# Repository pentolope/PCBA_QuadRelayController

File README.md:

# Four-Channel Relay Controller

Four-channel relay controller run by a small MCU on 5 V logic, switching external loads through screw terminals with the switched side kept apart from logic.

This repository seeds the design of a four-channel relay controller operated by a small MCU, with 5 V logic power and each relay switching an external load through screw terminals. The brief fixes the functional block list — input protection, transistor/MOSFET relay drivers, flyback suppression, status indication, and a programming interface — and imposes one layout-level constraint: the switched side must be physically separated from the logic side, with conservative clearances appropriate to a voltage rating the design agent selects and documents. Beyond those items nothing is pinned down. No relay, MCU, driver device, terminal block, protection part, programming standard, board outline, or stackup is named. The switched-side voltage rating is explicitly delegated — it is one "you select and document" — while the switched-side current rating and whether the load is AC or DC are never mentioned at all, and so are open by silence. Most of the architecture therefore belongs to the design agent; the brief supplies the block list and the separation constraint, not the implementation.

> **This board has not been designed.** There is no schematic, no layout and no
> part selection here — only the brief, a reading of the brief, and the
> scaffolding a design run needs. That is the intended state of this repository,
> not a gap in it.

## What the brief fixes, and what it leaves open

The brief pins down 13 requirements and deliberately leaves
20 decisions to whoever designs the board. The `Source` column says
which is which: `brief` is quoted from [BRIEF.md](BRIEF.md), `metadata` comes
from the benchmark catalogue, and `open` means the brief does not fix it.

| Aspect | Value | Source |
|---|---|---|
| Channel count | Four relay channels | brief |
| Controller | A small MCU; no family, part, package or core named | brief |
| Logic supply | 5 V | brief |
| Load connection | Each relay switches an external load through screw terminals | brief |
| Relay driver stage | Transistor/MOSFET relay drivers required; device and topology unspecified | brief |
| Flyback suppression | Required; suppression method not specified | brief |
| Input protection | Required; protected nodes and scheme not specified | brief |
| Status indication and programming interface | Both required; indication form, programming standard and the physical form of the interface all unspecified | brief |
| High/low voltage partition | Switched side physically separated from logic side | brief |
| Switched-side voltage rating, current rating and clearance values | Not fixed by the brief; the design agent selects and documents the voltage rating and chooses conservative clearances appropriate to it. The current rating and whether the load is AC or DC are not mentioned at all and are equally the agent's to decide. | open |
| Relay selection (coil voltage, contact form and rating, mounting style) | Design agent's choice; the brief names no relay | open |
| Board outline, size, mounting and terminal pitch | Design agent's choice; the brief states no mechanical envelope | open |
| Likely layer count | 2 | metadata |
| Category / difficulty / brief detail | industrial-control; difficulty 2; detail 2 | metadata |

The full split, with the verbatim brief text substantiating every fixed
requirement, is in [board/requirements.md](board/requirements.md) and
machine-readably in [board/requirements.json](board/requirements.json).

**Missing details are design freedom, not permission to fabricate unstated user
requirements.** A choice the brief left open is recorded as a decision, with its
reasoning — never promoted into a requirement.

## Benchmark position

| | |
|---|---|
| Benchmark id | 3 of 32 |
| Category | industrial-control |
| Difficulty | 2 / 5 |
| Brief detail | 2 / 5 |
| Likely layer count | 2 |
| Primary stressors | high/low voltage partition, relay flyback, creepage/clearance, terminal placement |

At difficulty 2 and detail 2 in the industrial-control category, this board tests whether an agent can execute a conventionally-shaped circuit while getting the physical discipline right rather than the component novelty. The listed stressors — high/low voltage partition, relay flyback, creepage/clearance, terminal placement — are all layout and rating problems, and the brief deliberately withholds the switched-side voltage rating so the agent must select one, choose clearances that are conservative and appropriate to it, and live with the consequences in the floorplan. The real test is whether the separation barrier and the clearance numbers rest on a stated basis or are merely asserted.

This repository is one of thirty-two. The suite, the protocol and the results
live in [PCBA_AutoDesignAndTest_Bench](https://github.com/pentolope/PCBA_AutoDesignAndTest_Bench).

## Repository layout

| Path | Contents |
|---|---|
| `BRIEF.md` | the supplied brief — authoritative, preserved byte for byte, never edited |
| `board/requirements.md` | what the brief fixes, what it leaves open, and where decisions get recorded |
| `board/requirements.json` | the same split, machine-readable, each fixed requirement bound to brief text |
| `board/manifest.template.json` | the toolkit's minimum manifest, pre-filled for this board |
| `board/toolchain.json` | where this board's build finds KiCad and the router |
| `benchmark/metadata.json` | the supplied catalogue entry — category, difficulty, detail, stressors |
| `docs/architecture.md` | the decisions this board must make, as questions, unanswered |
| `docs/sources.md` | the classes of evidence the design will have to cite |
| `docs/status.md` | what exists, what does not, and what is deliberately absent |
| `candidates/` | disposable search output, ignored by Git |
| `.claude/skills/` | the accountability-review skill [CLAUDE.md](CLAUDE.md) requires before a push |
| `tooling/PCBA_AutoDesignAndTest` | the shared verification/routing/release toolkit, as a pinned submodule |

## Getting the repository

The toolkit is a submodule and carries KiCad Routing Tools as a submodule of its
own, so clone recursively:

```bash
git clone --recursive https://github.com/pentolope/PCBA_QuadRelayController.git
```

```bash
git submodule update --init --recursive
```

## Designing the board

Generic verification, routing and release logic is **not** written here. It is
consumed from `tooling/PCBA_AutoDesignAndTest`, which is board-agnostic by
construction and must stay that way; this repository owns the board and nothing
else. Start from
[the toolkit's onboarding guide](tooling/PCBA_AutoDesignAndTest/examples/onboarding.md),
and see [CLAUDE.md](CLAUDE.md) for the rules a design run works under.

```bash
python3 tooling/PCBA_AutoDesignAndTest/run.py preflight
```

## Brief integrity

`BRIEF.md` SHA-256 `7ed0a0647777bf47b7bdb843b795a63dda5a91aa048535087b107b13f95b585d`

Every quotation in `board/requirements.json` is bound to those exact bytes. If
the brief ever changes, the bindings are stale by construction — which is the
point of recording the digest.

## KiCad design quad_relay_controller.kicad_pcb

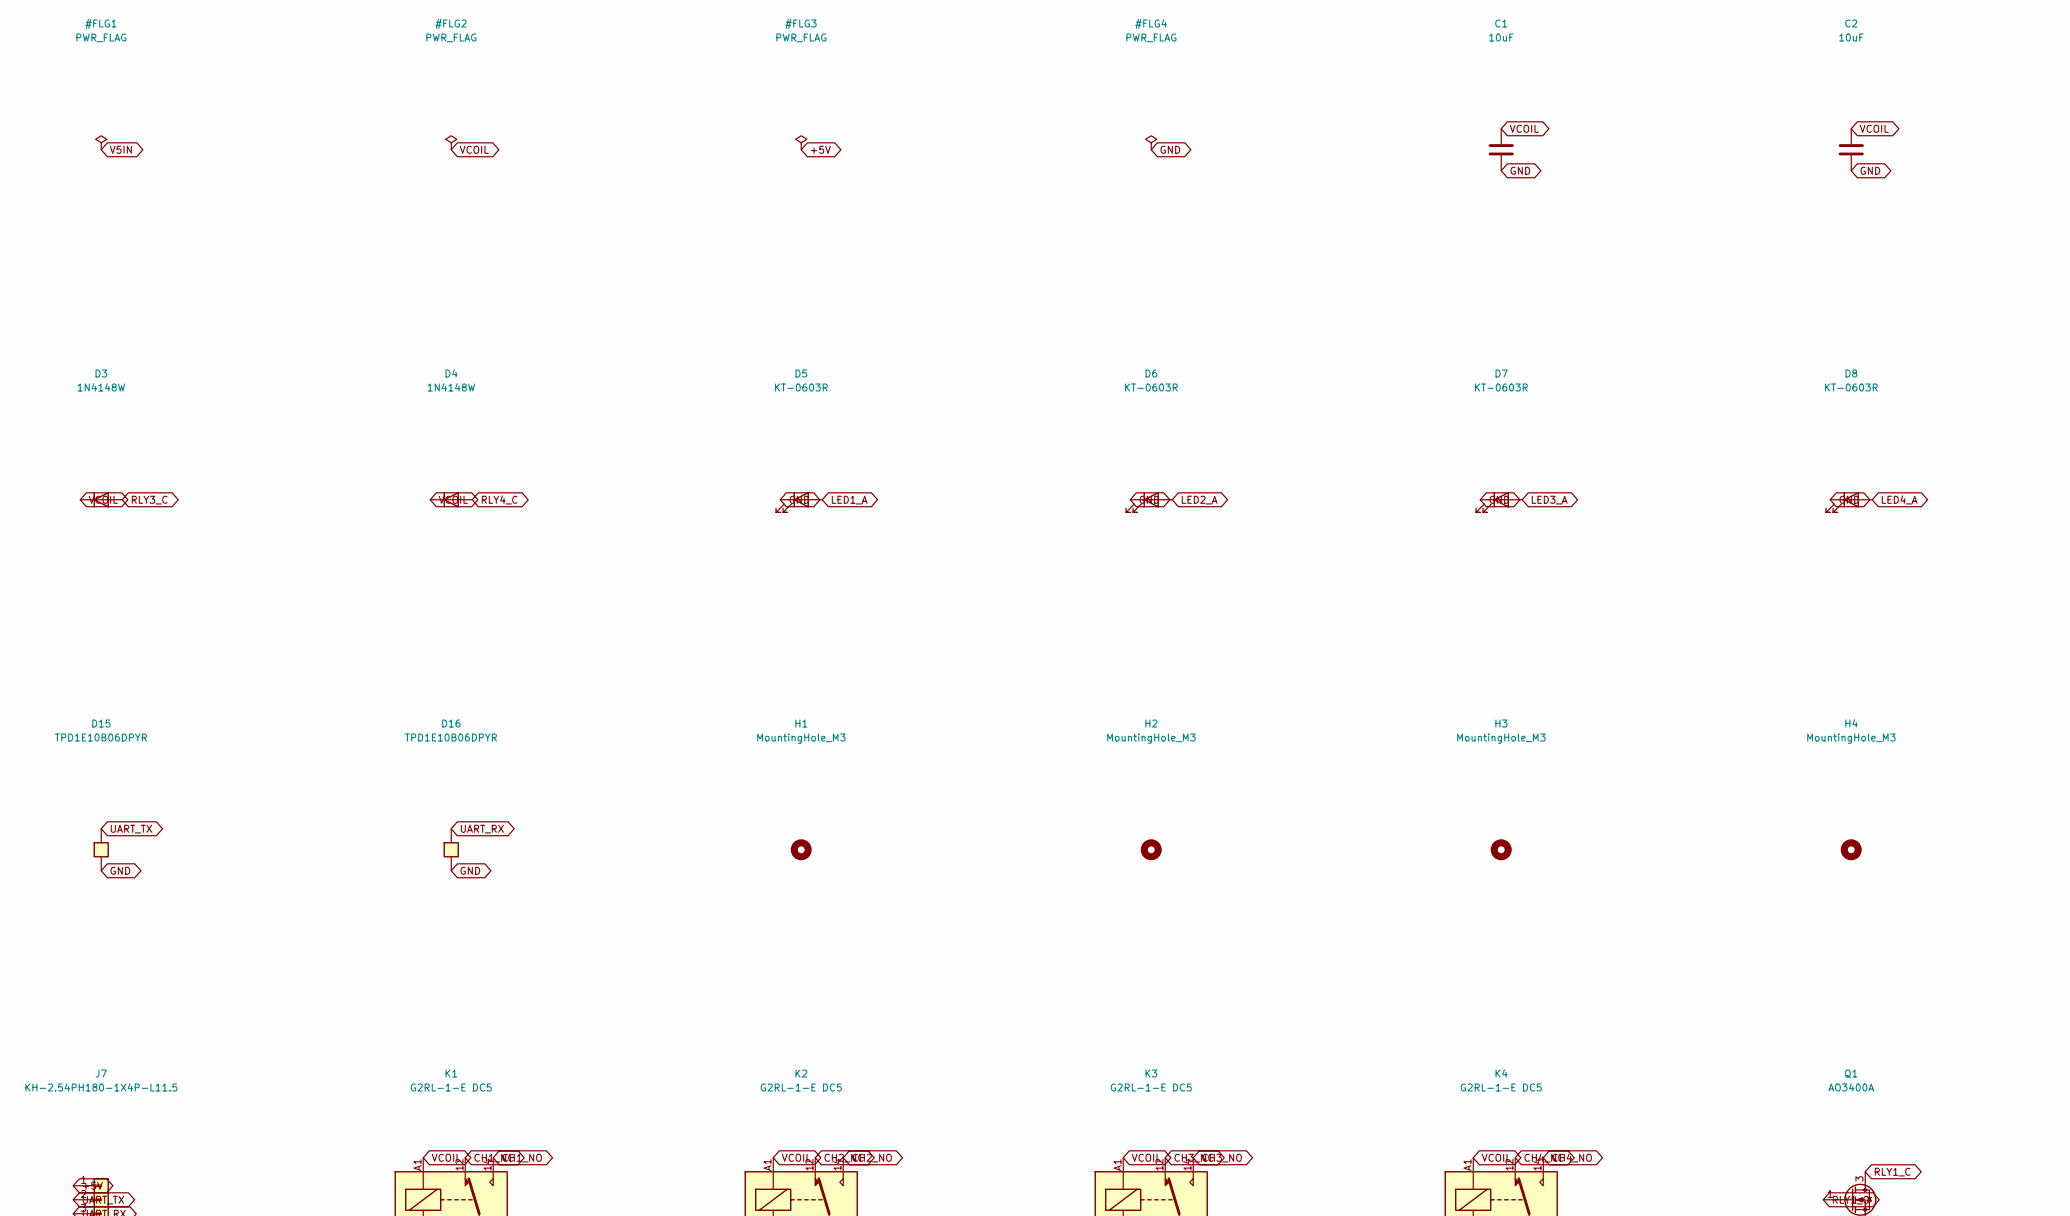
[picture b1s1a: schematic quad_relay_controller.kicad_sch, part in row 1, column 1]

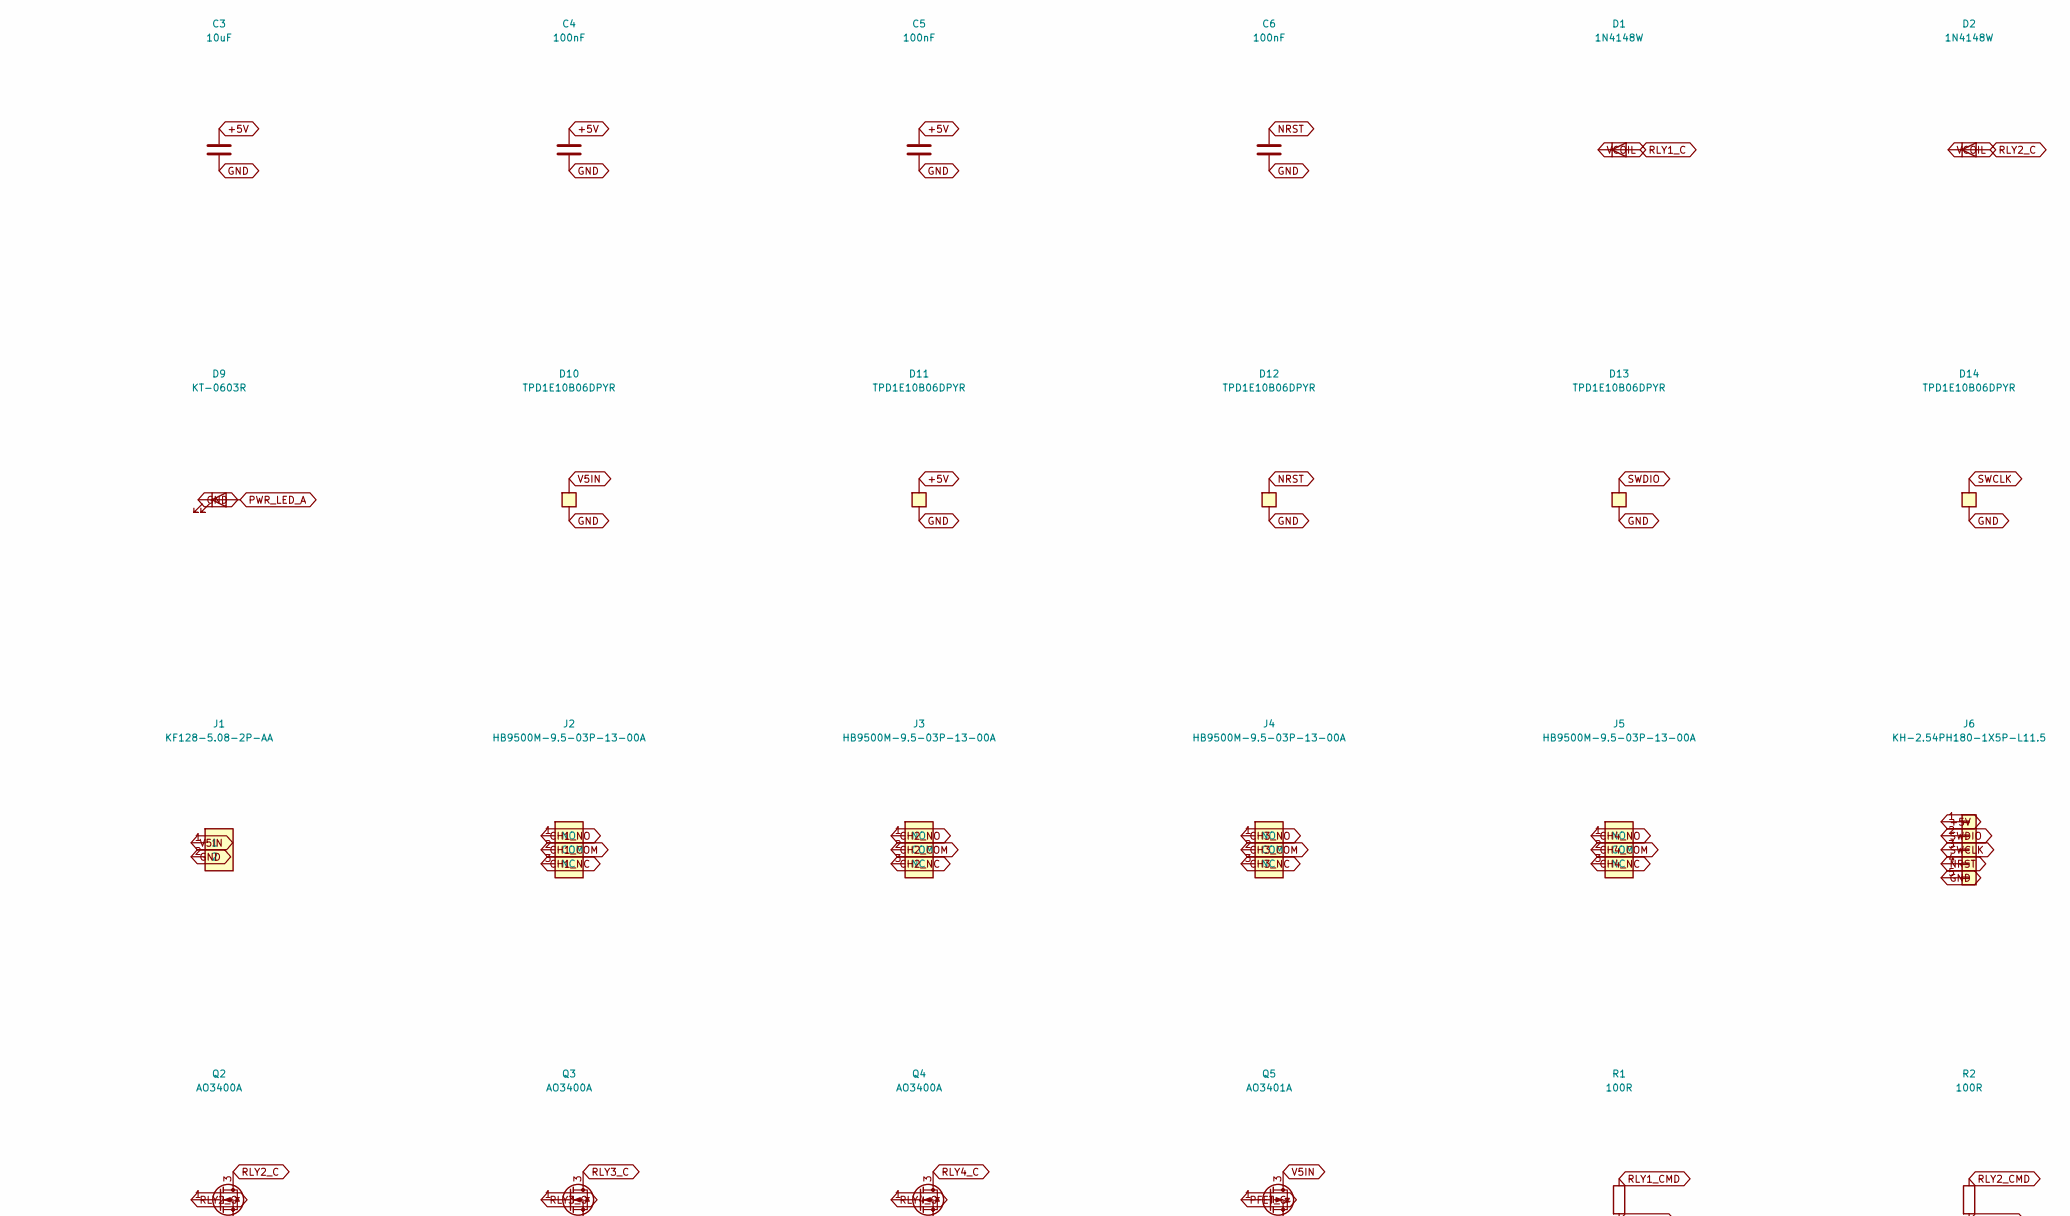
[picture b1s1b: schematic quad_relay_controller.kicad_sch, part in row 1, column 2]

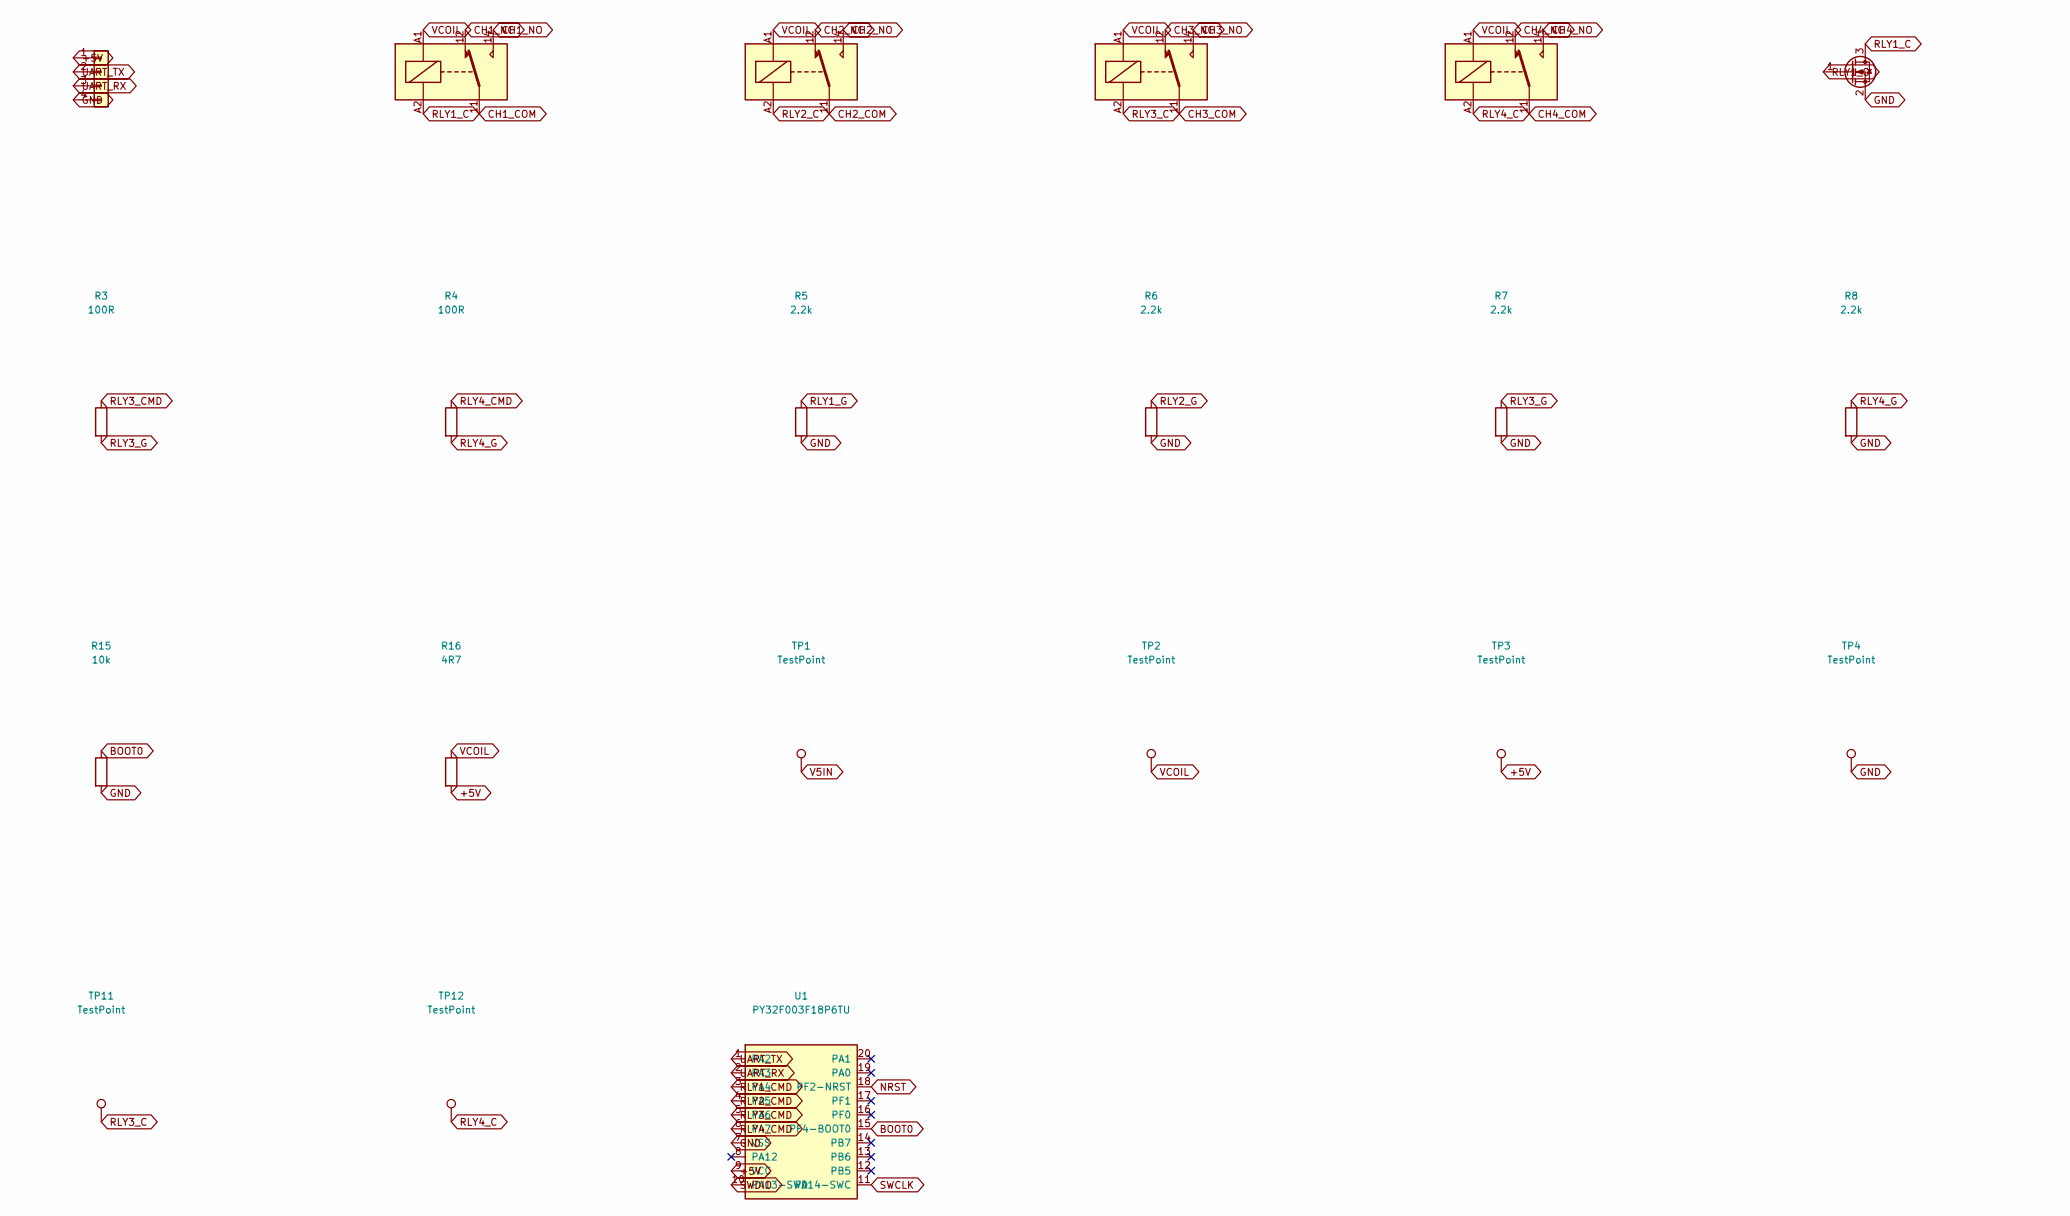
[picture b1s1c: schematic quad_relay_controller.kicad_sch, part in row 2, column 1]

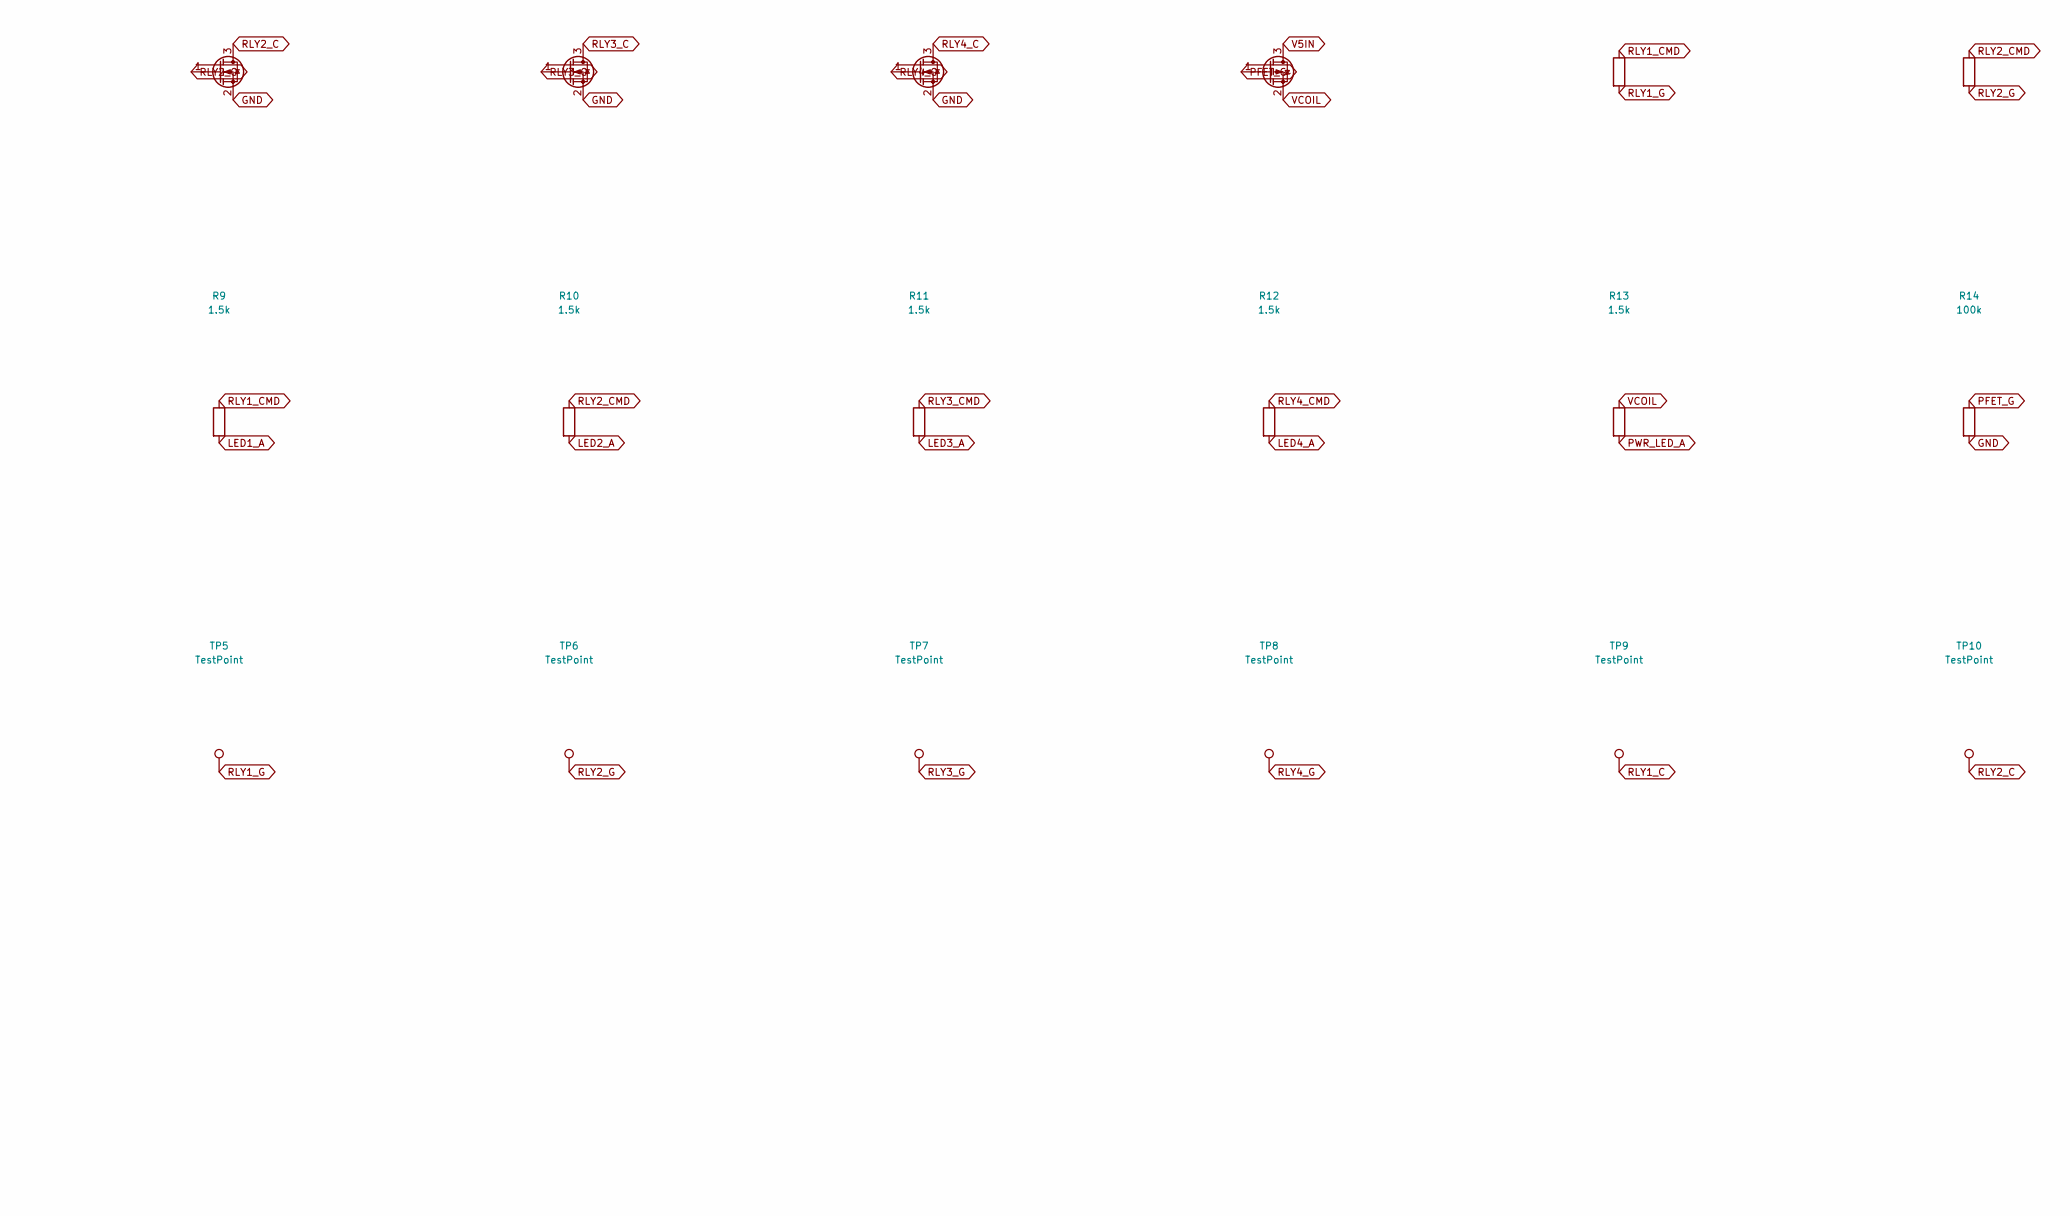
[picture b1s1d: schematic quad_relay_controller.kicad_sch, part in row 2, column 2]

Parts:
C1, C2, C3: 10uF; C_0805_2012Metric; MPN CL21A106KAYNNNE; LCSC C15850
C4, C5, C6: 100nF; C_0603_1608Metric; MPN CC0603KRX7R9BB104; LCSC C14663
D1, D2, D3, D4: 1N4148W; D_SOD-123; MPN 1N4148W; LCSC C81598
D5, D6, D7, D8, D9: KT-0603R; LED_0603_1608Metric; MPN KT-0603R; LCSC C2286
D10, D11, D12, D13, D14, D15, D16: TPD1E10B06DPYR; TI_X1SON-2_1.0x0.6mm_P0.65mm; MPN TPD1E10B06DPYR; LCSC C48260
H1, H2, H3, H4: MountingHole_M3; MountingHole_3.2mm_M3
J1: KF128-5.08-2P-AA; TerminalBlock_KF128-5.08_1x02_P5.08mm; MPN KF128-5.08-2P-AA; LCSC C474952
J2, J3, J4, J5: HB9500M-9.5-03P-13-00A; TerminalBlock_Ningbo-Kagnex_HB9500M_1x03_P9.5mm; MPN HB9500M-9.5-03P-13-00A; LCSC C162697
J6: KH-2.54PH180-1X5P-L11.5; PinHeader_1x05_P2.54mm_Vertical; MPN KH-2.54PH180-1X5P-L11.5; LCSC C2932699
J7: KH-2.54PH180-1X4P-L11.5; PinHeader_1x04_P2.54mm_Vertical; MPN KH-2.54PH180-1X4P-L11.5; LCSC C2905435
K1, K2, K3, K4: G2RL-1-E DC5; Relay_SPDT_Omron_G2RL-1-E; MPN G2RL-1-E DC5; LCSC C1524515
Q1, Q2, Q3, Q4: AO3400A; SOT-23; MPN AO3400A; LCSC C20917
Q5: AO3401A; SOT-23; MPN AO3401A; LCSC C15127
R1, R2, R3, R4: 100R; R_0603_1608Metric; MPN 0603WAF1000T5E; LCSC C22775
R5, R6, R7, R8: 2.2k; R_0603_1608Metric; MPN 0603WAF2201T5E; LCSC C4190
R9, R10, R11, R12, R13: 1.5k; R_0603_1608Metric; MPN 0603WAF1501T5E; LCSC C22843
R14: 100k; R_0603_1608Metric; MPN 0603WAF1003T5E; LCSC C25803
R15: 10k; R_0603_1608Metric; MPN 0603WAF1002T5E; LCSC C25804
R16: 4R7; R_0603_1608Metric; MPN 0603WAF470KT5E; LCSC C23164
TP1, TP2, TP3, TP4, TP5, TP6, TP7, TP8, TP9, TP10, TP11, TP12: TestPoint; TestPoint_Pad_D1.0mm
U1: PY32F003F18P6TU; TSSOP-20_4.4x6.5mm_P0.65mm; MPN PY32F003F18P6TU; LCSC C5379864

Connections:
+5V: C3.1, C4.1, C5.1, D11.2 (A2), J6.1, J7.1, R16.2, TP3.1, U1.9 (VCC)
BOOT0: R15.1, U1.15 (PF4-BOOT0)
CH1_COM: J2.2 (COM), K1.11
CH1_NC: J2.3 (NC), K1.12
CH1_NO: J2.1 (NO), K1.14
CH2_COM: J3.2 (COM), K2.11
CH2_NC: J3.3 (NC), K2.12
CH2_NO: J3.1 (NO), K2.14
CH3_COM: J4.2 (COM), K3.11
CH3_NC: J4.3 (NC), K3.12
CH3_NO: J4.1 (NO), K3.14
CH4_COM: J5.2 (COM), K4.11
CH4_NC: J5.3 (NC), K4.12
CH4_NO: J5.1 (NO), K4.14
GND: C1.2, C2.2, C3.2, C4.2, C5.2, C6.2, D5.1 (K), D6.1 (K), D7.1 (K), D8.1 (K), D9.1 (K), D10.1 (A1), D11.1 (A1), D12.1 (A1), D13.1 (A1), D14.1 (A1), D15.1 (A1), D16.1 (A1), J1.2, J6.5, J7.4, Q1.2 (S), Q2.2 (S), Q3.2 (S), Q4.2 (S), R5.2, R6.2, R7.2, R8.2, R14.2, R15.2, TP4.1, U1.7 (VSS)
LED1_A: D5.2 (A), R9.2
LED2_A: D6.2 (A), R10.2
LED3_A: D7.2 (A), R11.2
LED4_A: D8.2 (A), R12.2
NRST: C6.1, D12.2 (A2), J6.4, U1.18 (PF2-NRST)
PFET_G: Q5.1 (G), R14.1
PWR_LED_A: D9.2 (A), R13.2
RLY1_C: D1.2 (A), K1.A2, Q1.3 (D), TP9.1
RLY1_CMD: R1.1, R9.1, U1.3 (PA4)
RLY1_G: Q1.1 (G), R1.2, R5.1, TP5.1
RLY2_C: D2.2 (A), K2.A2, Q2.3 (D), TP10.1
RLY2_CMD: R2.1, R10.1, U1.4 (PA5)
RLY2_G: Q2.1 (G), R2.2, R6.1, TP6.1
RLY3_C: D3.2 (A), K3.A2, Q3.3 (D), TP11.1
RLY3_CMD: R3.1, R11.1, U1.5 (PA6)
RLY3_G: Q3.1 (G), R3.2, R7.1, TP7.1
RLY4_C: D4.2 (A), K4.A2, Q4.3 (D), TP12.1
RLY4_CMD: R4.1, R12.1, U1.6 (PA7)
RLY4_G: Q4.1 (G), R4.2, R8.1, TP8.1
SWCLK: D14.2 (A2), J6.3, U1.11 (PA14-SWC)
SWDIO: D13.2 (A2), J6.2, U1.10 (PA13-SWD)
UART_RX: D16.2 (A2), J7.3, U1.2 (PA3)
UART_TX: D15.2 (A2), J7.2, U1.1 (PA2)
V5IN: D10.2 (A2), J1.1, Q5.3 (D), TP1.1
VCOIL: C1.1, C2.1, D1.1 (K), D2.1 (K), D3.1 (K), D4.1 (K), K1.A1, K2.A1, K3.A1, K4.A1, Q5.2 (S), R13.1, R16.1, TP2.1

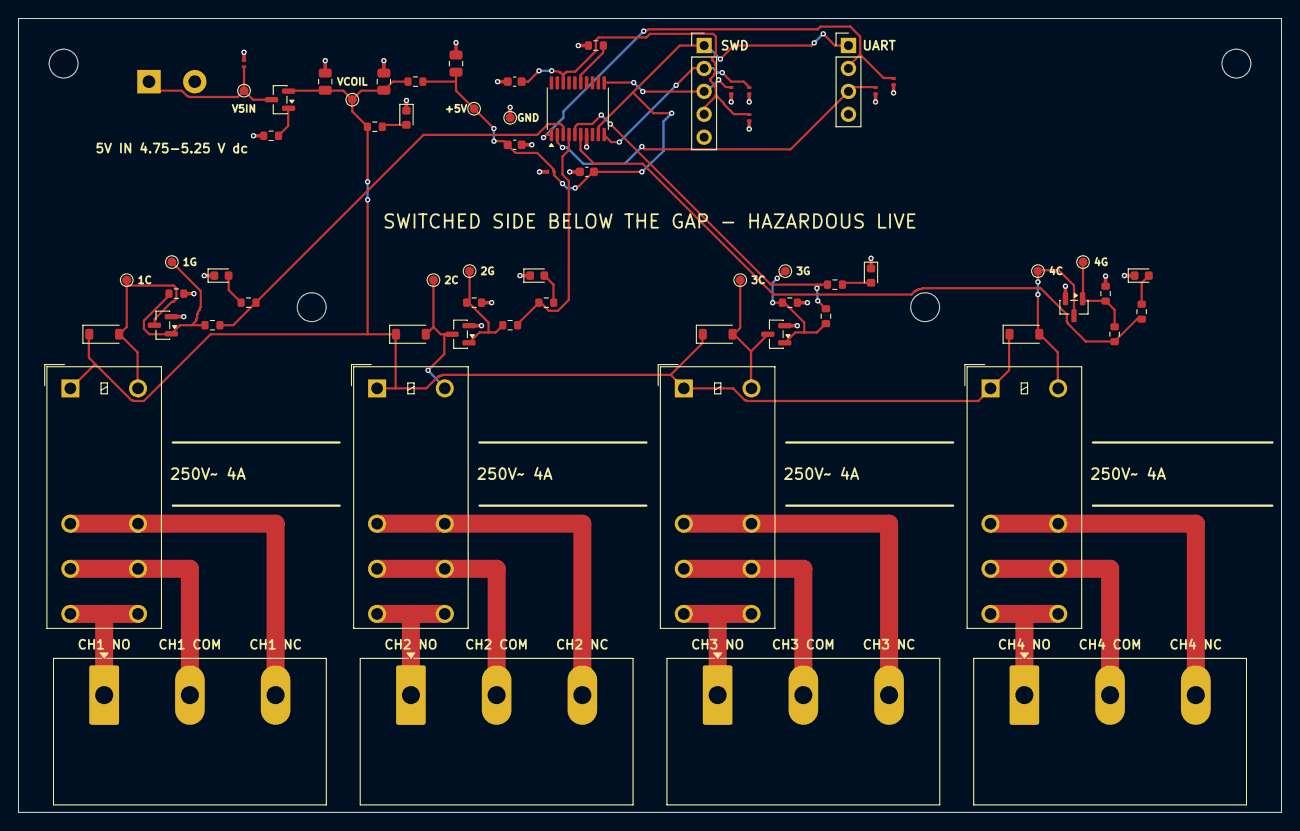
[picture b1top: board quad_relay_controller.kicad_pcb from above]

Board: 2 copper layers, 140.0 x 88.0 mm, 71 parts (0 on the bottom side), 40 nets.
